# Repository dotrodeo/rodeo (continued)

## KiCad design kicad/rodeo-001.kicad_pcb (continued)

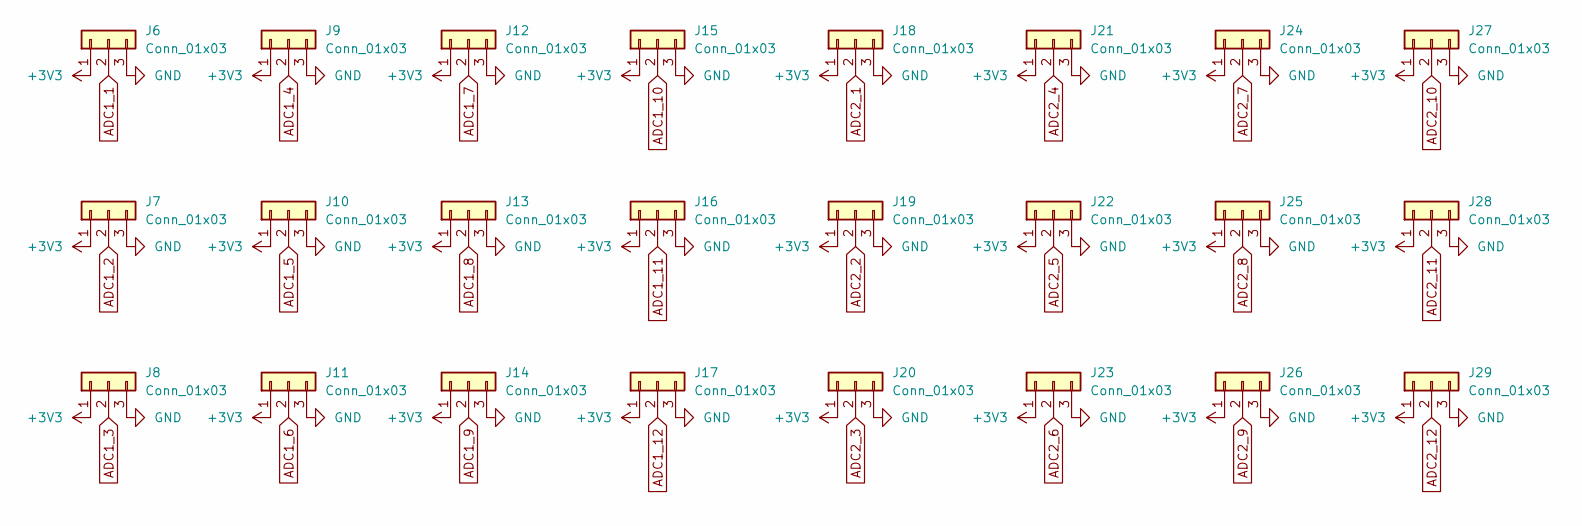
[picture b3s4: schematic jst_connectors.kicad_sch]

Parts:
J6, J7, J8, J9, J10, J11, J12, J13, J14, J15, J16, J17, J18, J19, J20, J21, J22, J23, J24, J25, J26, J27, J28, J29: Conn_01x03; JST_SH_BM03B-SRSS-TB_1x03-1MP_P1.00mm_Vertical

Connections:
+3V3: J6.1, J7.1, J8.1, J9.1, J10.1, J11.1, J12.1, J13.1, J14.1, J15.1, J16.1, J17.1, J18.1, J19.1, J20.1, J21.1, J22.1, J23.1, J24.1, J25.1, J26.1, J27.1, J28.1, J29.1; also elsewhere on the board
ADC1_1: J6.2; also elsewhere on the board
ADC1_2: J7.2; also elsewhere on the board
ADC1_3: J8.2; also elsewhere on the board
ADC1_4: J9.2; also elsewhere on the board
ADC1_5: J10.2; also elsewhere on the board
ADC1_6: J11.2; also elsewhere on the board
ADC1_7: J12.2; also elsewhere on the board
ADC1_8: J13.2; also elsewhere on the board
ADC1_9: J14.2; also elsewhere on the board
ADC1_10: J15.2; also elsewhere on the board
ADC1_11: J16.2; also elsewhere on the board
ADC1_12: J17.2; also elsewhere on the board
ADC2_1: J18.2; also elsewhere on the board
ADC2_2: J19.2; also elsewhere on the board
ADC2_3: J20.2; also elsewhere on the board
ADC2_4: J21.2; also elsewhere on the board
ADC2_5: J22.2; also elsewhere on the board
ADC2_6: J23.2; also elsewhere on the board
ADC2_7: J24.2; also elsewhere on the board
ADC2_8: J25.2; also elsewhere on the board
ADC2_9: J26.2; also elsewhere on the board
ADC2_10: J27.2; also elsewhere on the board
ADC2_11: J28.2; also elsewhere on the board
ADC2_12: J29.2; also elsewhere on the board
GND: J6.3, J7.3, J8.3, J9.3, J10.3, J11.3, J12.3, J13.3, J14.3, J15.3, J16.3, J17.3, J18.3, J19.3, J20.3, J21.3, J22.3, J23.3, J24.3, J25.3, J26.3, J27.3, J28.3, J29.3; also elsewhere on the board

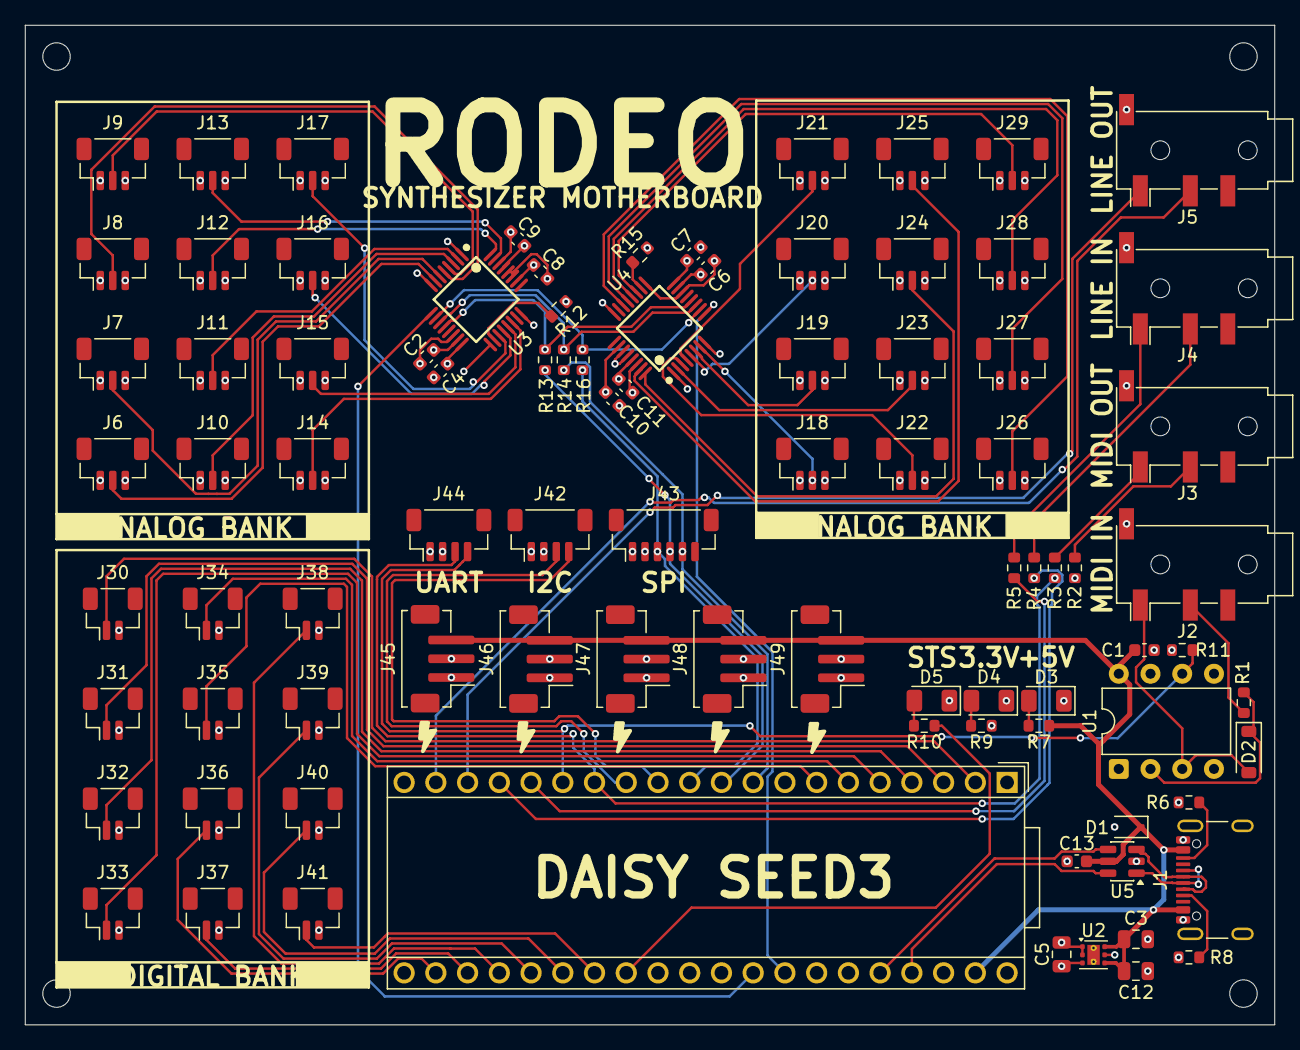
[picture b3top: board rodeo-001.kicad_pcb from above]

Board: 4 copper layers, 100.0 x 80.0 mm, 89 parts (0 on the bottom side), 74 nets.

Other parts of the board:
J42: I2C; JST_SH_BM04B-SRSS-TB_1x04-1MP_P1.00mm_Vertical
J43: SPI; JST_SH_BM06B-SRSS-TB_1x06-1MP_P1.00mm_Vertical
J44: UART; JST_SH_BM04B-SRSS-TB_1x04-1MP_P1.00mm_Vertical

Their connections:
+3V3: J42.2, J43.1, J44.1; also elsewhere on the board
GND: J42.1, J43.2, J44.2; also elsewhere on the board
I2C_SCL: J42.4; also elsewhere on the board
I2C_SDA: J42.3; also elsewhere on the board
SPI_MISO: J43.4; also elsewhere on the board
SPI_MOSI: J43.3; also elsewhere on the board
SPI_SCK: J43.5; also elsewhere on the board
UART_RX: J44.4; also elsewhere on the board
UART_TX: J44.3; also elsewhere on the board

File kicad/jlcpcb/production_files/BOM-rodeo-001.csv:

Comment,Designator,Footprint,LCSC,Quantity
0.1u,"C1,C13,C2,C4,C6,C7",C_0603_1608Metric,C125205,6
100R,"R2,R3,R4,R5",R_0603_1608Metric,C22775,4
10K,"R12,R15",R_0603_1608Metric,C25804,2
1K,"R10,R7,R9",R_0603_1608Metric,C21190,3
1N4148W,D2,D_SOD-123,C81598,1
1u,"C11,C9",C_0603_1608Metric,C15849,2
1u,"C3,C5",C_0805_2012Metric,C28323,2
220R,R1,R_0603_1608Metric,C22962,1
22u,C12,C_0805_2012Metric,C45783,1
330n,"C10,C8",C_0603_1608Metric,C1615,2
33R,"R13,R14,R16",R_0603_1608Metric,C23140,3
470R,R11,R_0603_1608Metric,C23179,1
5K1,"R6,R8",R_0603_1608Metric,C23186,2
6N138,U1,DIP-8_W7.62mm,C3001991,1
AudioJack4,"J2,J3,J4,J5",Jack_3.5mm_PJ320D_Horizontal,C431535,4
Conn_01x02,"J30,J31,J32,J33,J34,J35,J36,J37,J38,J39,J40,J41",JST_SH_BM02B-SRSS-TB_1x02-1MP_P1.00mm_Vertical,C160388,12
Conn_01x03,"J10,J11,J12,J13,J14,J15,J16,J17,J18,J19,J20,J21,J22,J23,J24,J25,J26,J27,J28,J29,J6,J7,J8,J9",JST_SH_BM03B-SRSS-TB_1x03-1MP_P1.00mm_Vertical,C160389,24
Conn_01x03,"J45,J46,J47,J48,J49",JST_ZH_B3B-ZR-SM4-TF_1x03-1MP_P1.50mm_Vertical,C489717,5
D_TVS,D1,D_SOD-323,C2687132,1
I2C,J42,JST_SH_BM04B-SRSS-TB_1x04-1MP_P1.00mm_Vertical,C160390,1
LED,"D3,D4,D5",LED_1206_3216Metric,C125085,3
SPI,J43,JST_SH_BM06B-SRSS-TB_1x06-1MP_P1.00mm_Vertical,C160392,1
TLV76733DRVx,U2,WSON-6-1EP_2x2mm_P0.65mm_EP1x1.6mm_ThermalVias,C2848334,1
UART,J44,JST_SH_BM04B-SRSS-TB_1x04-1MP_P1.00mm_Vertical,C160390,1
USBLC6-2SC6,U5,SOT-23-6,C7519,1
USB_C_Receptacle,J1,USB_C_Receptacle_GCT_USB4105-xx-A_16P_TopMnt_Horizontal,C3020560,1
~,"U3,U4",TQFP-32_L5.0-W5.0-P0.50-LS7.0-BL,C2670120,2
Electrosmith_Daisy_Seed_Rev4,A1,Electrosmith_Daisy_Seed,,1
